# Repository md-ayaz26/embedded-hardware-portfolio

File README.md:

# Embedded Systems & Hardware Engineering Portfolio

> **Mohammad Ayaz Riyaz**  
> 2nd Year B.Tech — Electronics & Telecommunication Engineering (ENTC)  
> **PVG's College of Engineering and Technology (PVGCOET), Pune**  
> Focus: Embedded Systems | Firmware (C / Embedded C) | PCB Design (KiCad) | IoT

---

## 🎯 Technical Focus & Skillset

- **Languages:** C, Embedded C, Python (basics/scripting)
- **EDA & Hardware Tools:** KiCad 10 (Schematic capture, PCB layout, DRC/ERC, Gerber generation)
- **Target Architectures & Boards:** ESP32, STM32 (ARM Cortex-M), ATmega / Arduino
- **Peripherals & Protocols:** GPIO, Timers, Interrupts, ADC, PWM, UART, I2C, SPI, CAN bus
- **Tools & Workflow:** Git, GitHub, VS Code, PlatformIO / STM32CubeIDE

---

## 🚀 Featured Hardware Projects

### 🔌 [Sensor Power & I2C Baseboard (v1.0)](./kicad-hardware/Sensor_Power_Baseboard/Sensor_Power_Baseboard/)

A modular 2-layer PCB designed from scratch in KiCad 10 to supply regulated 3.3V power via USB-C and provide a terminated I2C bus header for environmental and motion sensors (OLED, BME280, MPU6050).

- **Power Input:** USB-C with $5.1\text{ k}\Omega$ CC pull-down resistors for USB-PD source negotiation.
- **Regulation:** AMS1117-3.3 LDO with $10\,\mu\text{F} / 100\text{ nF}$ input decoupling and $22\,\mu\text{F} / 100\text{ nF}$ output stability capacitors.
- **Sensor Bus:** 4-pin $2.54\text{ mm}$ pitch header with dedicated $4.7\text{ k}\Omega$ I2C pull-up resistors.
- **Status:** ✅ Completed (Passed ERC & DRC with 0 errors; Gerbers packaged and ready for fabrication).

---

## 📁 Repository Structure & Projects

```text
├── firmware/
│   └── bitwise-c/              # [✅ Completed] Low-level bit masking, register flipping, and GPIO drills
├── kicad-hardware/
│   └── Sensor_Power_Baseboard/ # [✅ Completed] 2-layer custom USB-C to 3.3V power & sensor baseboard
└── notes/                      # Technical notes on protocols, datasheets, and circuit analysis
```

| # | Project / Module | Domain | Status | Key Highlights |
|---|---|---|---|---|
| 01 | **[Register & Bitwise Manipulation](./firmware/bitwise-c/)** | Embedded C | ✅ Completed | Direct register bit-masking, bit-flipping, port manipulation |
| 02 | **[Sensor Power & I2C Baseboard](./kicad-hardware/Sensor_Power_Baseboard/Sensor_Power_Baseboard/)** | KiCad Hardware | ✅ Completed | 5V to 3.3V LDO regulator, USB-C CC logic, I2C sensor bus, Gerbers |
| 03 | **I2C Sensor Driver from Scratch** | Firmware | ⚪ Planned | Reading sensor data via bare register/protocol calls |
| 04 | **Automotive / Industrial CAN Node** | Embedded / Auto | ⚪ Planned | CAN bus transceiver integration and packet telemetry |

---

## 📬 Contact & Links
- **GitHub:** [md-ayaz26](https://github.com/md-ayaz26)

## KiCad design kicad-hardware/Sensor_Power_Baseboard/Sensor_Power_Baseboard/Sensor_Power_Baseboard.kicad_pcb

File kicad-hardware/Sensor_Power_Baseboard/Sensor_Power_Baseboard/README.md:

# Sensor Power & I2C Baseboard (v1.0)

A modular, production-ready power delivery and sensor breakout PCB designed in KiCad 10.

Designed by **Mohammad Ayaz Riyaz** (2nd Year ENTC @ PVGCOET Pune).

---

## 📸 3D Hardware Renders

| Top-Down View | Perspective 3D View |
| :---: | :---: |
|  |  |

---

## ⚡ Circuit & Layout Specifications

### 1. USB-C 5V Power Sink
- **Connector:** 16-Pin USB-C Receptacle (`USB_C_Receptacle_HRO_TYPE-C-31-M-12`).
- **Negotiation:** Dual $5.1\text{ k}\Omega$ pull-down resistors ($R_1, R_2$) on CC1 and CC2.
  - *Engineering Rationale:* Ensures modern USB Type-C power supplies / PD chargers recognize the board as a valid power sink and turn on the 5V rail.
- **Orientation:** Outward-facing connector on the left board edge allowing standard cable clearance.

### 2. Voltage Regulation (5V $\rightarrow$ 3.3V)
- **LDO Regulator:** `AMS1117-3.3` (SOT-223 package with ground heatsink tab).
- **Filtering & Decoupling:**
  - **Input:** $10\,\mu\text{F}$ bulk capacitor ($C_1$) + $100\text{ nF}$ high-frequency bypass capacitor ($C_2$) placed right at $V_{in}$ to attenuate input transients.
  - **Output:** $22\,\mu\text{F}$ capacitor ($C_3$) + $100\text{ nF}$ bypass capacitor ($C_4$) for regulator feedback loop stability.
- **Power Indicator:** Status LED ($D_1$) with a $1\text{ k}\Omega$ series current-limiting resistor ($R_3$).

### 3. I2C Sensor Interface Header
- **Pinout:** 4-pin $2.54\text{ mm}$ pitch male header (`3V3`, `GND`, `SDA`, `SCL`) compatible with OLED displays (SSD1306), environmental sensors (BME280), and IMUs (MPU6050).
- **Pull-Ups:** Dedicated $4.7\text{ k}\Omega$ pull-up resistors ($R_4, R_5$) on SDA and SCL to guarantee sharp clock and data rise times on open-drain signals.

---

## 🛠️ PCB Manufacturing Specifications

| Parameter | Specification |
| :--- | :--- |
| **Dimensions** | Approx. $40\text{ mm} \times 20\text{ mm}$ |
| **Layer Count** | 2 Layers (`F.Cu` signals/power, `B.Cu` solid ground plane) |
| **PCB Thickness** | $1.6\text{ mm}$ |
| **Surface Finish** | HASL with lead / Lead-Free HASL / ENIG |
| **Solder Mask** | Matte Green |
| **Silkscreen** | White |
| **Design Rules** | Checked & passed with **0 DRC Errors** & **0 Unconnected Nets** |

---

## 📦 Manufacturing & Design Files
- **KiCad Schematic Source:** `Sensor_Power_Baseboard.kicad_sch`
- **KiCad PCB Layout:** `Sensor_Power_Baseboard.kicad_pcb`
- **Schematic PDF:** [Sensor_Power_Baseboard.pdf](./Sensor_Power_Baseboard.pdf)
- **Production Gerbers & Drill ZIP:** [Sensor_Power_Baseboard_Gerbers.zip](./production/Sensor_Power_Baseboard_Gerbers.zip) *(Ready to upload to JLCPCB, PCBWay, or LionCircuits)*

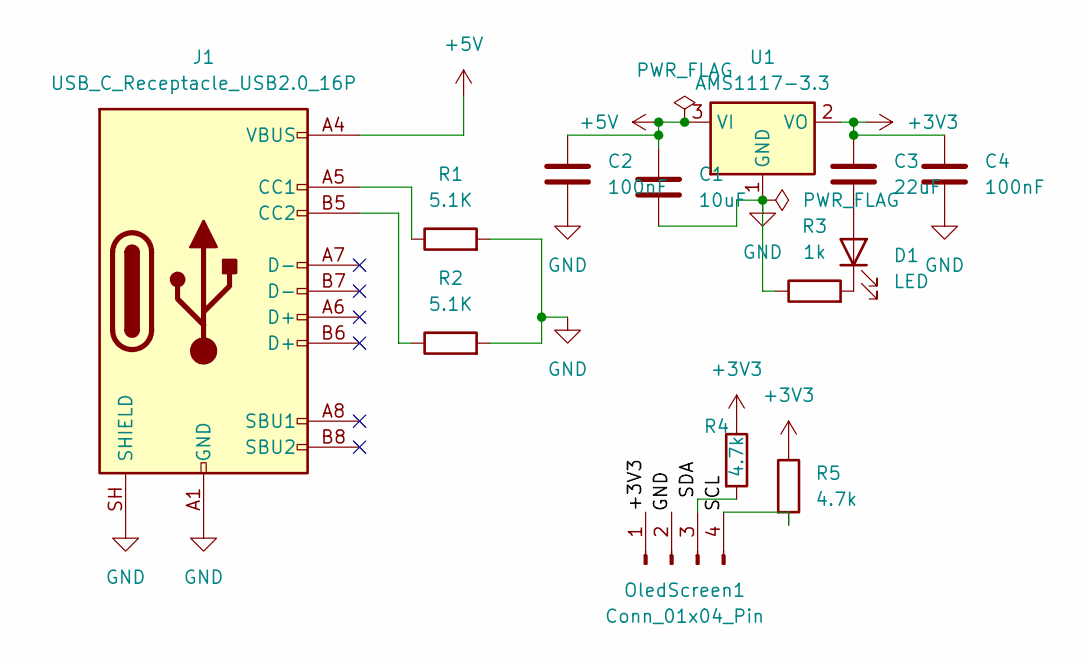
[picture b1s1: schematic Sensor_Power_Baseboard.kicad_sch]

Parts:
C1: 10uF; C_0805_2012Metric
C2, C4: 100nF; C_0805_2012Metric
C3: 22uF; C_0805_2012Metric
D1: LED; LED_0805_2012Metric
J1: USB_C_Receptacle_USB2.0_16P; USB_C_Receptacle_HRO_TYPE-C-31-M-12
OledScreen1: Conn_01x04_Pin; PinHeader_1x04_P2.54mm_Vertical
R1, R2: 5.1K; R_0805_2012Metric
R3: 1k; R_0805_2012Metric
R4, R5: 4.7k; R_0805_2012Metric
U1: AMS1117-3.3; SOT-223-3_TabPin2

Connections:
+3V3: C3.1, C4.1, OledScreen1.1, R4.1, R5.1, U1.2 (VO)
+5V: C1.1, C2.2, J1.A4 (VBUS), J1.A9 (VBUS), J1.B4 (VBUS), J1.B9 (VBUS), U1.3 (VI)
/SCL: OledScreen1.4, R5.2
/SDA: OledScreen1.3, R4.2
GND: C1.2, C2.1, C4.2, J1.A1 (GND), J1.A12 (GND), J1.B1 (GND), J1.B12 (GND), J1.SH (SHIELD), OledScreen1.2, R1.2, R2.2, R3.1, U1.1 (GND)
unnamed: C3.2, D1.2 (A)
unnamed: D1.1 (K), R3.2
unnamed: J1.A5 (CC1), R1.1
unnamed: J1.B5 (CC2), R2.1

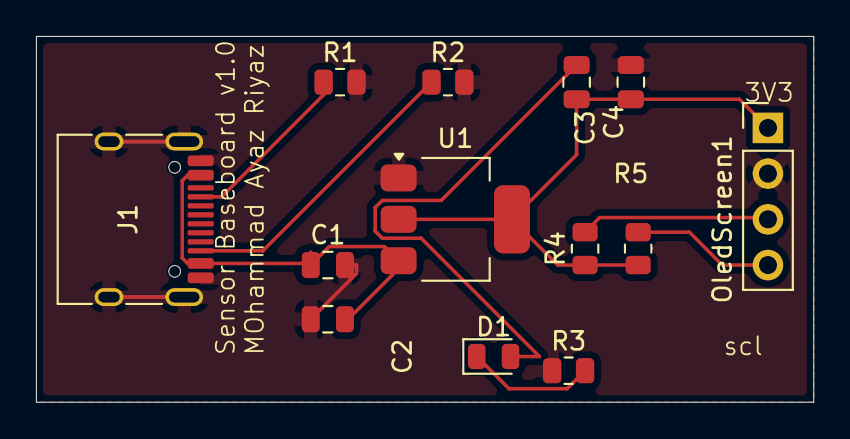
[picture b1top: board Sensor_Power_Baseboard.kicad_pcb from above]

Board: 2 copper layers, 43.2 x 20.3 mm, 13 parts (0 on the bottom side), 9 nets.
